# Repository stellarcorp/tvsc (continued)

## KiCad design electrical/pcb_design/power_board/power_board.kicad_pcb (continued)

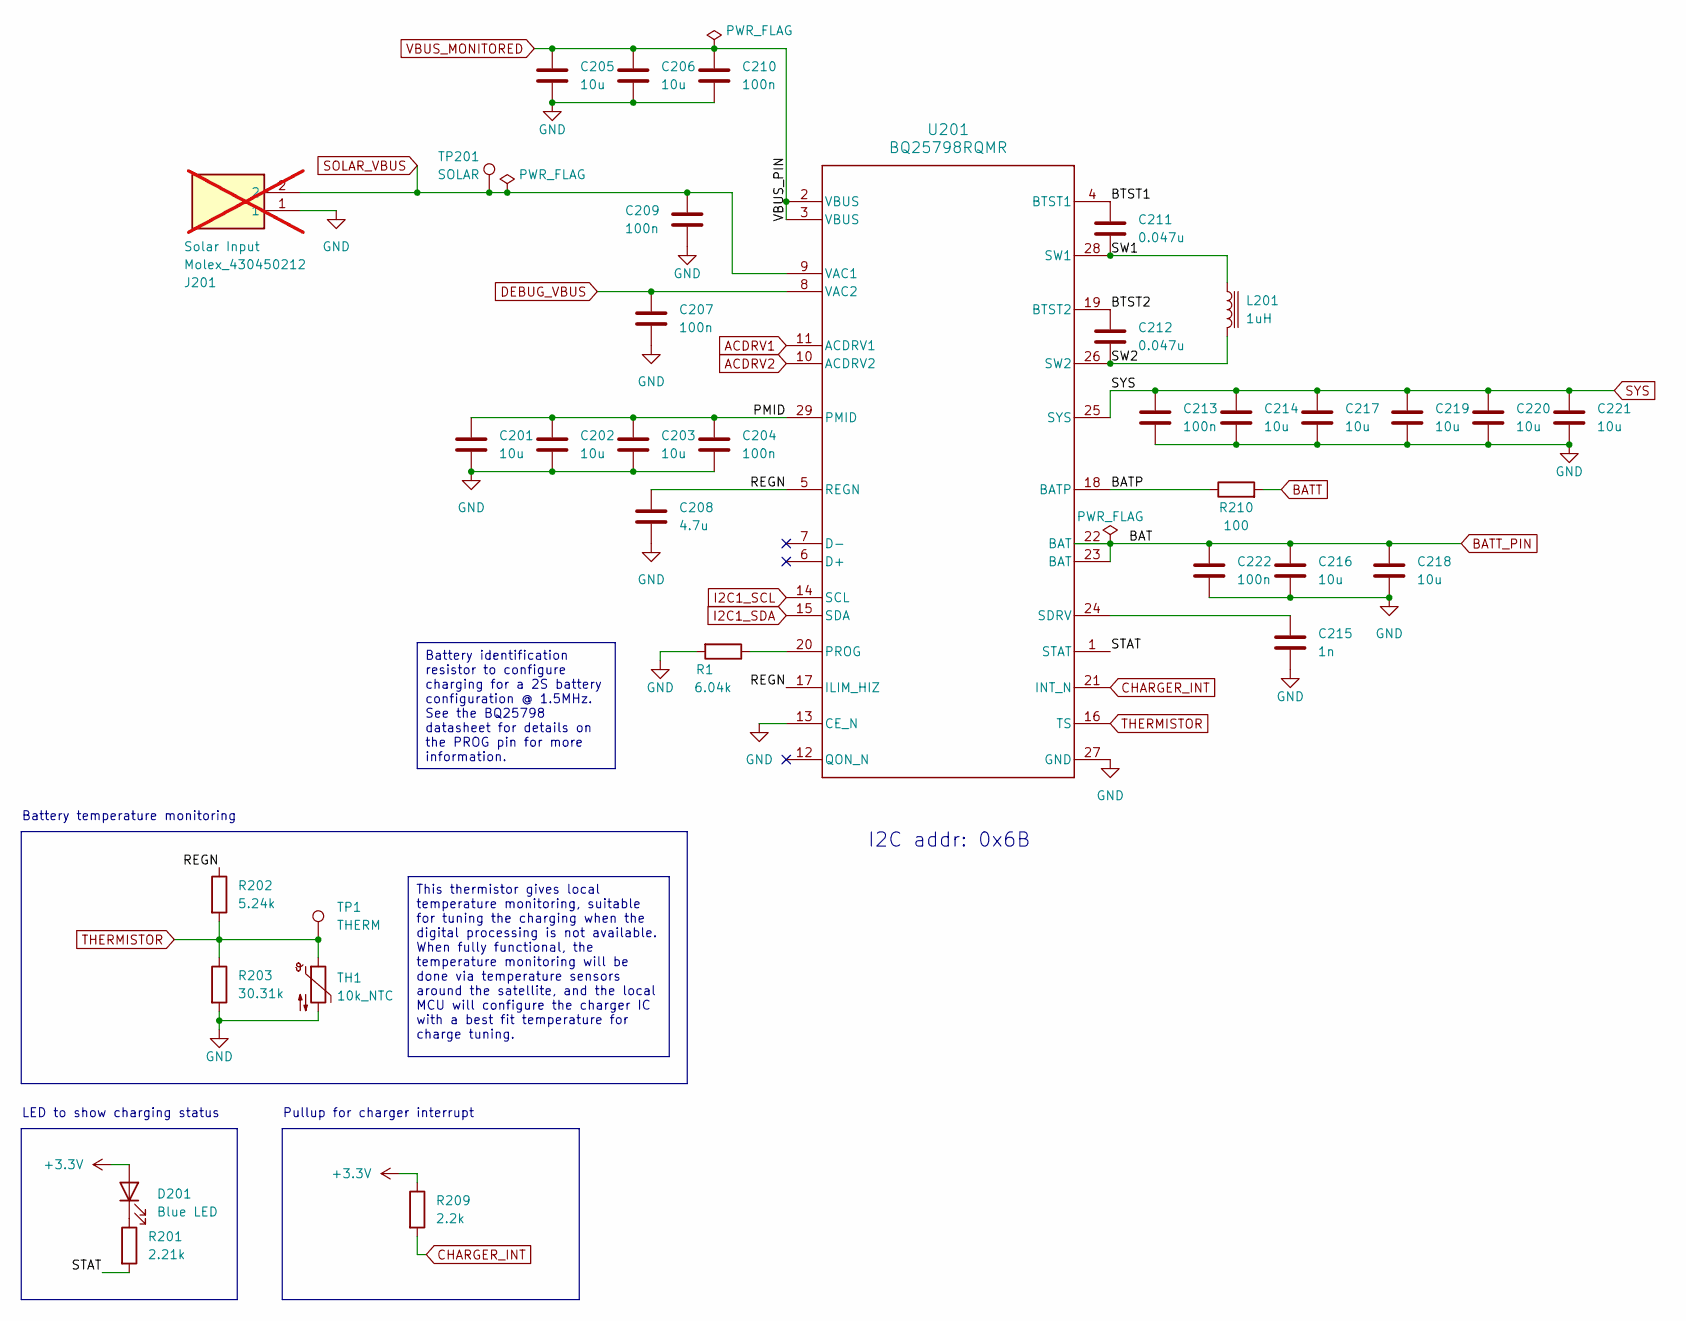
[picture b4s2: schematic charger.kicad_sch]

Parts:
C201, C202, C203, C205, C206, C214, C217, C219, C220, C221: 10u; Nondescript_C_0603_1608Metric; Manufacturer Part Number GRM188R61E106KA73D
C204, C207, C209, C210, C213, C222: 100n; Nondescript_C_0402_1005Metric; Manufacturer Part Number GCM155R71H104KE02J
C208: 4.7u; Nondescript_C_0603_1608Metric; MPN C86016
C211, C212: 0.047u; Nondescript_C_0402_1005Metric; Manufacturer Part Number CL05B473KA5NNNC
C215: 1n; Nondescript_C_0402_1005Metric; MPN C76947
C216, C218: 10u; Nondescript_C_0603_1608Metric; MPN C344022
D201: Blue LED; LED_0603_1608Metric; MPN C72041
J201: Molex_430450212; Manufacturer Part Number 430450212; not fitted
L201: 1uH; TDK_SPM6530; MPN C87572
R1: 6.04k; R_0603_1608Metric; MPN C114631
R201: 2.21k; Nondescript_R_0402_1005Metric; MPN C305298
R202: 5.24k; R_0402_1005Metric; MPN C170332
R203: 30.31k; R_0603_1608Metric; MPN C423049
R209: 2.2k; R_0402_1005Metric; MPN C517529
R210: 100; R_0603_1608Metric; MPN C105588
TH1: 10k_NTC; R_0402_1005Metric; MPN C209959
TP1: THERM; TestPoint_Pad_D2.5mm
TP201: SOLAR; TestPoint_Pad_D2.5mm
U201: BQ25798RQMR; RQM0029A-MFG; MPN C2876593

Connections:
+3.3V: D201.2 (A), R209.1; also elsewhere on the board
/Charger/BATP: R210.1, U201.18 (BATP)
/Charger/BTST1: C211.1, U201.4 (BTST1)
/Charger/BTST2: C212.1, U201.19 (BTST2)
/Charger/PMID: C201.1, C202.1, C203.1, C204.1, U201.29 (PMID)
/Charger/REGN: C208.1, R202.1, U201.5 (REGN), U201.17 (ILIM_HIZ)
/Charger/STAT: R201.2, U201.1 (STAT)
/Charger/SW1: C211.2, L201.1, U201.28 (SW1)
/Charger/SW2: C212.2, L201.2, U201.26 (SW2)
ACDRV1: U201.11 (ACDRV1); also elsewhere on the board
ACDRV2: U201.10 (ACDRV2); also elsewhere on the board
BATT: R210.2; also elsewhere on the board
BATT_PIN: C216.1, C218.1, C222.1, U201.22 (BAT), U201.23 (BAT); also elsewhere on the board
CHARGER_INT: R209.2, U201.21 (INT_N); also elsewhere on the board
DEBUG_VBUS: C207.1, U201.8 (VAC2); also elsewhere on the board
GND: C201.2, C202.2, C203.2, C204.2, C205.2, C206.2, C207.2, C208.2, C209.2, C210.2, C213.2, C214.2, C215.2, C216.2, C217.2, C218.2, C219.2, C220.2, C221.2, C222.2, J201.1, R1.2, R203.2, TH1.2, U201.13 (CE_N), U201.27 (GND); also elsewhere on the board
I2C1_SCL: U201.14 (SCL); also elsewhere on the board
I2C1_SDA: U201.15 (SDA); also elsewhere on the board
unnamed: D201.1 (K), R201.1
unnamed: R1.1, U201.20 (PROG)
unnamed: C215.1, U201.24 (SDRV)
SOLAR_VBUS: C209.1, J201.2, TP201.1, U201.9 (VAC1); also elsewhere on the board
SYS: C213.1, C214.1, C217.1, C219.1, C220.1, C221.1, U201.25 (SYS); also elsewhere on the board
THERMISTOR: R202.2, R203.1, TH1.1, TP1.1, U201.16 (TS); also elsewhere on the board
VBUS_MONITORED: C205.1, C206.1, C210.1, U201.2 (VBUS), U201.3 (VBUS); also elsewhere on the board

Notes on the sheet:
Battery identification resistor to configure charging for a 2S battery configuration @ 1.5MHz. See the BQ25798 datasheet for details on the PROG pin for more information.
This thermistor gives local temperature monitoring, suitable for tuning the charging when the digital processing is not available. When fully functional, the temperature monitoring will be done via temperature sensors around the satellite, and the local MCU will configure the charger IC with a best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
Pullup for charger interrupt
Battery temperature monitoring
I2C addr: 0x6B
LED to show charging status

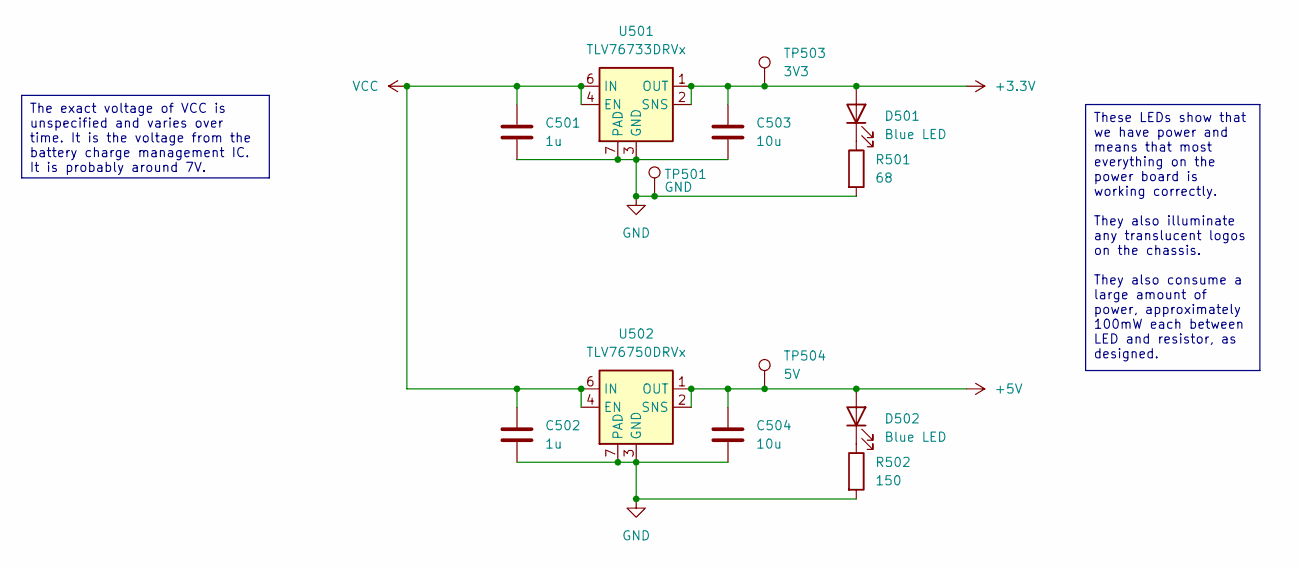
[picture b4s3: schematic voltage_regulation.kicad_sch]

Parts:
C501, C502: 1u; C_0805_2012Metric; MPN C726584
C503, C504: 10u; Nondescript_C_0603_1608Metric; MPN C344022
D501, D502: Blue LED; LED_0603_1608Metric; MPN C72041
R501: 68; R_0402_1005Metric; MPN C163455
R502: 150; R_0402_1005Metric; MPN C138054
TP501: GND; TestPoint_Pad_D2.5mm
TP503: 3V3; TestPoint_Pad_D2.5mm
TP504: 5V; TestPoint_Pad_D2.5mm
U501: TLV76733DRVx; WSON-6-1EP_2x2mm_P0.65mm_EP1x1.6mm_ThermalVias; MPN C2848334
U502: TLV76750DRVx; WSON-6-1EP_2x2mm_P0.65mm_EP1x1.6mm_ThermalVias; Manufacturer Part Number TLV76750DRVR

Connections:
+3.3V: C503.1, D501.2 (A), TP503.1, U501.1 (OUT), U501.2 (SNS); also elsewhere on the board
+5V: C504.1, D502.2 (A), TP504.1, U502.1 (OUT), U502.2 (SNS); also elsewhere on the board
GND: C501.2, C502.2, C503.2, C504.2, R501.2, R502.2, TP501.1, U501.3 (GND), U501.5 (GND), U501.7 (PAD), U502.3 (GND), U502.5 (GND), U502.7 (PAD); also elsewhere on the board
unnamed: D501.1 (K), R501.1
unnamed: D502.1 (K), R502.1
VCC: C501.1, C502.1, U501.4 (EN), U501.6 (IN), U502.4 (EN), U502.6 (IN); also elsewhere on the board

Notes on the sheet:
These LEDs show that we have power and means that most everything on the power board is working correctly. They also illuminate any translucent logos on the chassis. They also consume a large amount of power, approximately 100mW each between LED and resistor, as designed.
The exact voltage of VCC is unspecified and varies over time. It is the voltage from the battery charge management IC. It is probably around 7V.

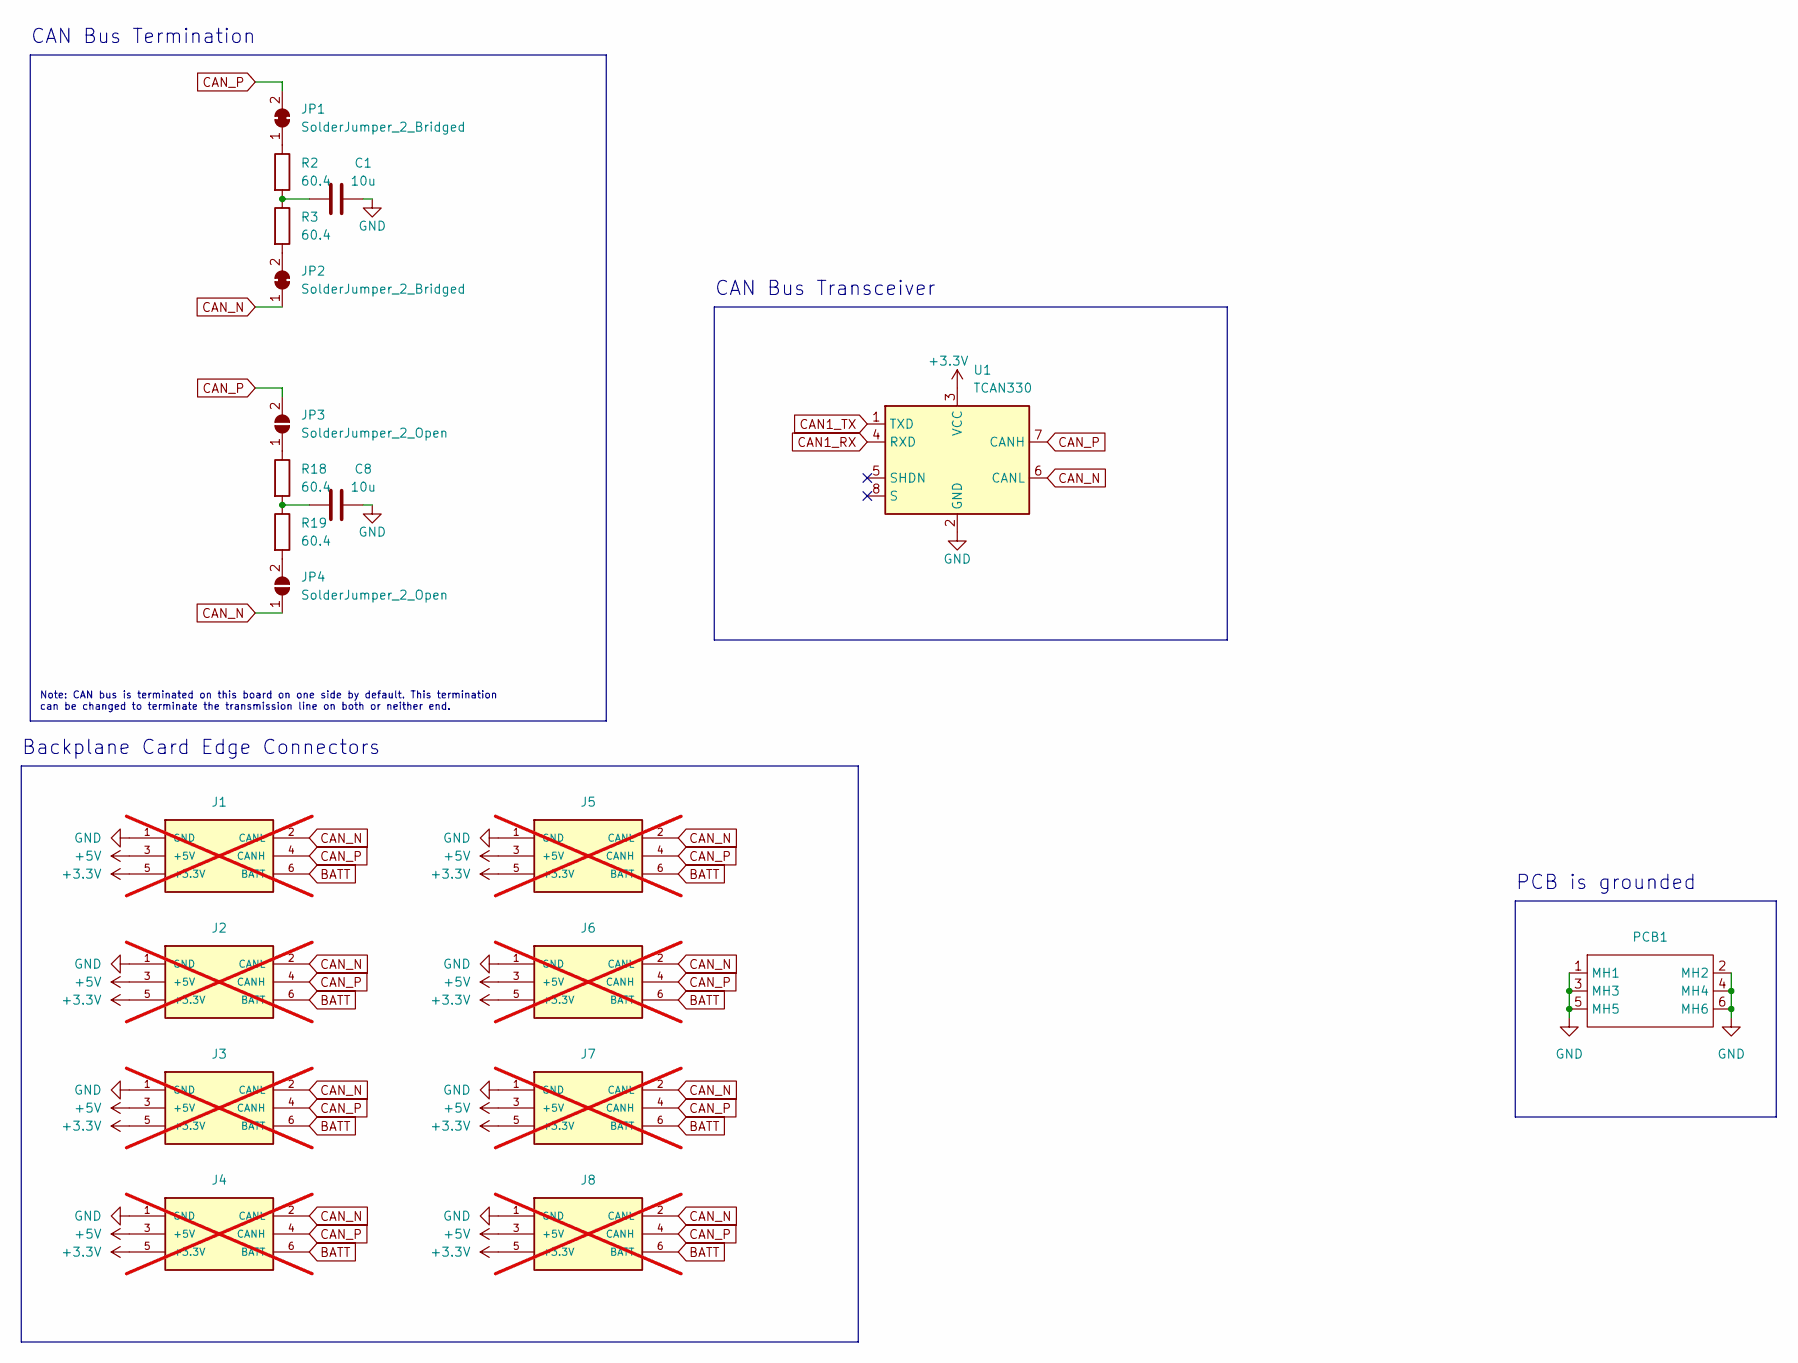
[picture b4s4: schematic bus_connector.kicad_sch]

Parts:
C1, C8: 10u; Nondescript_C_0603_1608Metric; MPN C344022
J1, J2, J3, J4, J5, J6, J7, J8: TE_Connectivity_7-5530843-7; Manufacturer Part Number 7-5530843-7; not fitted
JP1, JP2: SolderJumper_2_Bridged; SolderJumper-2_P1.3mm_Bridged_RoundedPad1.0x1.5mm
JP3, JP4: SolderJumper_2_Open; SolderJumper-2_P1.3mm_Open_RoundedPad1.0x1.5mm
PCB1: Interior_Side_Panel_PCB_Shape
R2, R3, R18, R19: 60.4; R_0402_1005Metric; MPN C60310
U1: TCAN330; SOT-23-8; Manufacturer Part Number TCAN330DCNR

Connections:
+3.3V: J1.5 (+3.3V), J2.5 (+3.3V), J3.5 (+3.3V), J4.5 (+3.3V), J5.5 (+3.3V), J6.5 (+3.3V), J7.5 (+3.3V), J8.5 (+3.3V), U1.3 (VCC); also elsewhere on the board
+5V: J1.3 (+5V), J2.3 (+5V), J3.3 (+5V), J4.3 (+5V), J5.3 (+5V), J6.3 (+5V), J7.3 (+5V), J8.3 (+5V); also elsewhere on the board
BATT: J1.6 (BATT), J2.6 (BATT), J3.6 (BATT), J4.6 (BATT), J5.6 (BATT), J6.6 (BATT), J7.6 (BATT), J8.6 (BATT); also elsewhere on the board
CAN1_RX: U1.4 (RXD); also elsewhere on the board
CAN1_TX: U1.1 (TXD); also elsewhere on the board
CAN_N: J1.2 (CANL), J2.2 (CANL), J3.2 (CANL), J4.2 (CANL), J5.2 (CANL), J6.2 (CANL), J7.2 (CANL), J8.2 (CANL), JP2.1 (A), JP4.1 (A), U1.6 (CANL)
CAN_P: J1.4 (CANH), J2.4 (CANH), J3.4 (CANH), J4.4 (CANH), J5.4 (CANH), J6.4 (CANH), J7.4 (CANH), J8.4 (CANH), JP1.2 (B), JP3.2 (B), U1.7 (CANH)
GND: C1.2, C8.2, J1.1 (GND), J2.1 (GND), J3.1 (GND), J4.1 (GND), J5.1 (GND), J6.1 (GND), J7.1 (GND), J8.1 (GND), PCB1.1 (MH1), PCB1.2 (MH2), PCB1.3 (MH3), PCB1.4 (MH4), PCB1.5 (MH5), PCB1.6 (MH6), U1.2 (GND); also elsewhere on the board
unnamed: C1.1, R2.2, R3.1
unnamed: C8.1, R18.2, R19.1
unnamed: JP1.1 (A), R2.1
unnamed: JP2.2 (B), R3.2
unnamed: JP3.1 (A), R18.1
unnamed: JP4.2 (B), R19.2

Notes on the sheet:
Note: CAN bus is terminated on this board on one side by default. This termination can be changed to terminate the transmission line on both or neither end.
PCB is grounded
CAN Bus Transceiver
CAN Bus Termination
Backplane Card Edge Connectors

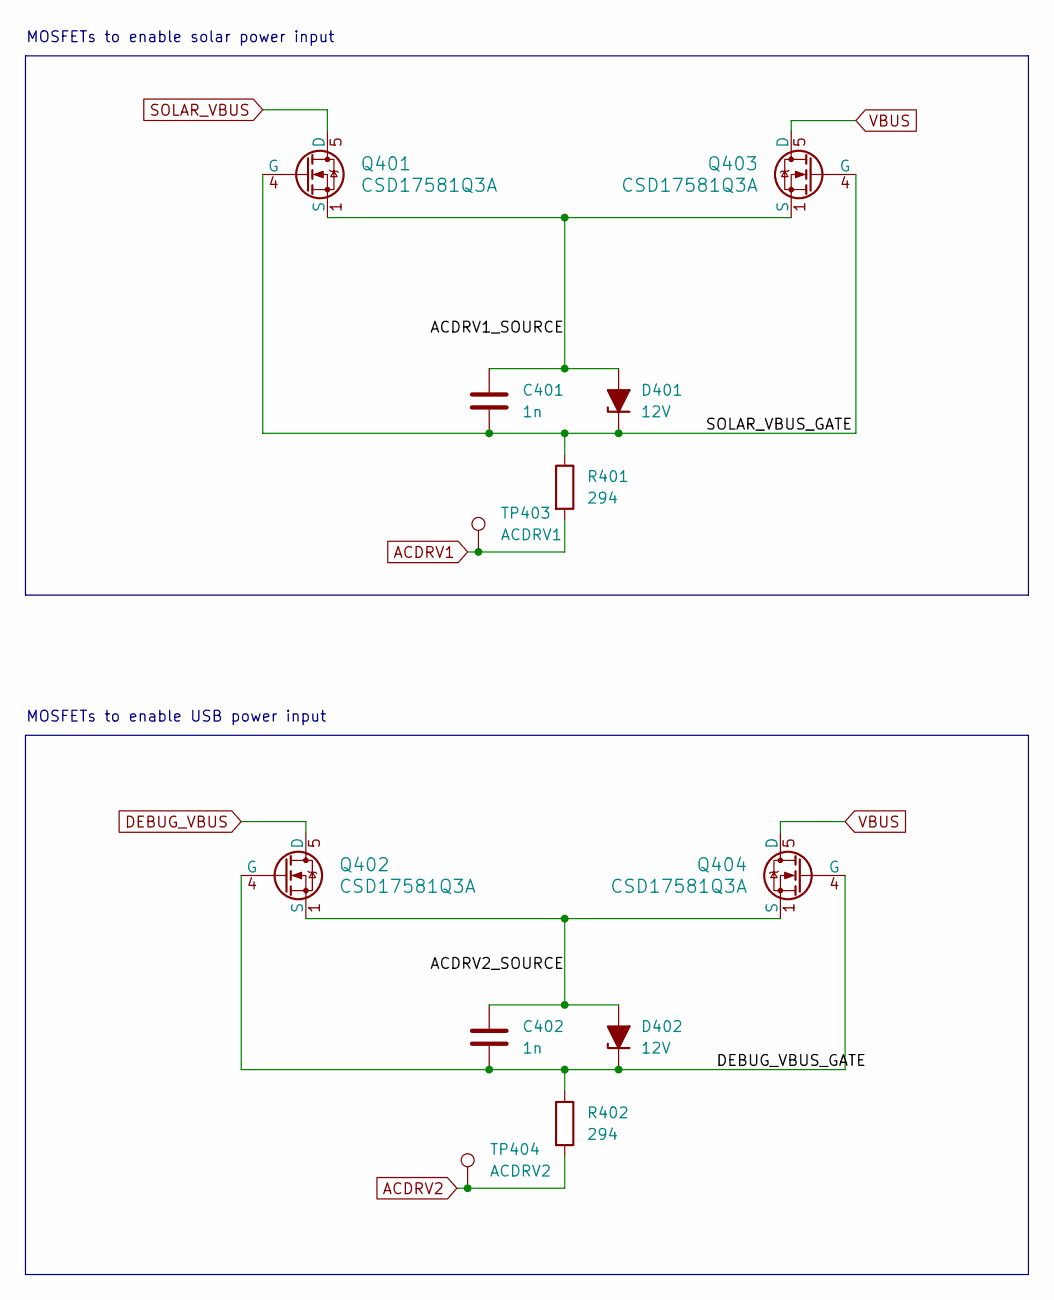
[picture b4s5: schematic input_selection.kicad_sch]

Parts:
C401, C402: 1n; Nondescript_C_0402_1005Metric; Manufacturer Part Number GRM1555C1H102JA01D
D401, D402: 12V; D_SOD-523; Manufacturer Part Number BZT52C12T-7
Q401, Q402, Q403, Q404: CSD17581Q3A; Q3A_TEX; MPN C2861705
R401, R402: 294; R_0603_1608Metric; Manufacturer Part Number RC0603FR-07294RL
TP403: ACDRV1; TestPoint_Pad_D2.5mm
TP404: ACDRV2; TestPoint_Pad_D2.5mm

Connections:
/Input Selection/ACDRV1_SOURCE: C401.1, D401.2 (A), Q401.1 (S), Q403.1 (S)
/Input Selection/ACDRV2_SOURCE: C402.1, D402.2 (A), Q402.1 (S), Q404.1 (S)
/Input Selection/DEBUG_VBUS_GATE: C402.2, D402.1 (K), Q402.4 (G), Q404.4 (G), R402.1
/Input Selection/SOLAR_VBUS_GATE: C401.2, D401.1 (K), Q401.4 (G), Q403.4 (G), R401.1
ACDRV1: R401.2, TP403.1; also elsewhere on the board
ACDRV2: R402.2, TP404.1; also elsewhere on the board
DEBUG_VBUS: Q402.5 (D); also elsewhere on the board
SOLAR_VBUS: Q401.5 (D); also elsewhere on the board
VBUS: Q403.5 (D), Q404.5 (D); also elsewhere on the board

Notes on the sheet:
MOSFETs to enable USB power input
MOSFETs to enable solar power input

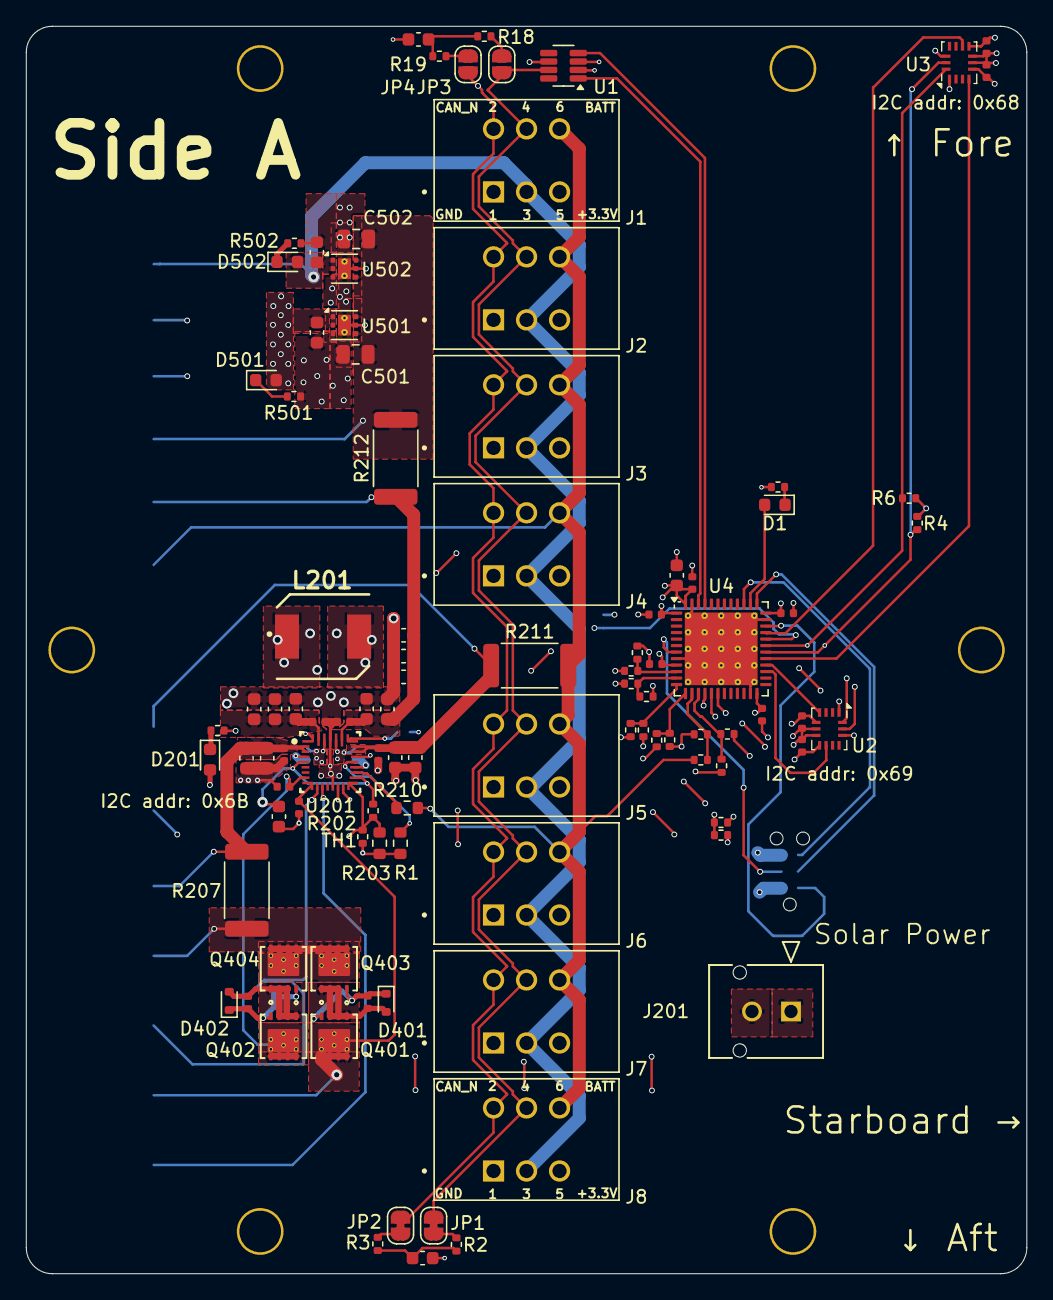
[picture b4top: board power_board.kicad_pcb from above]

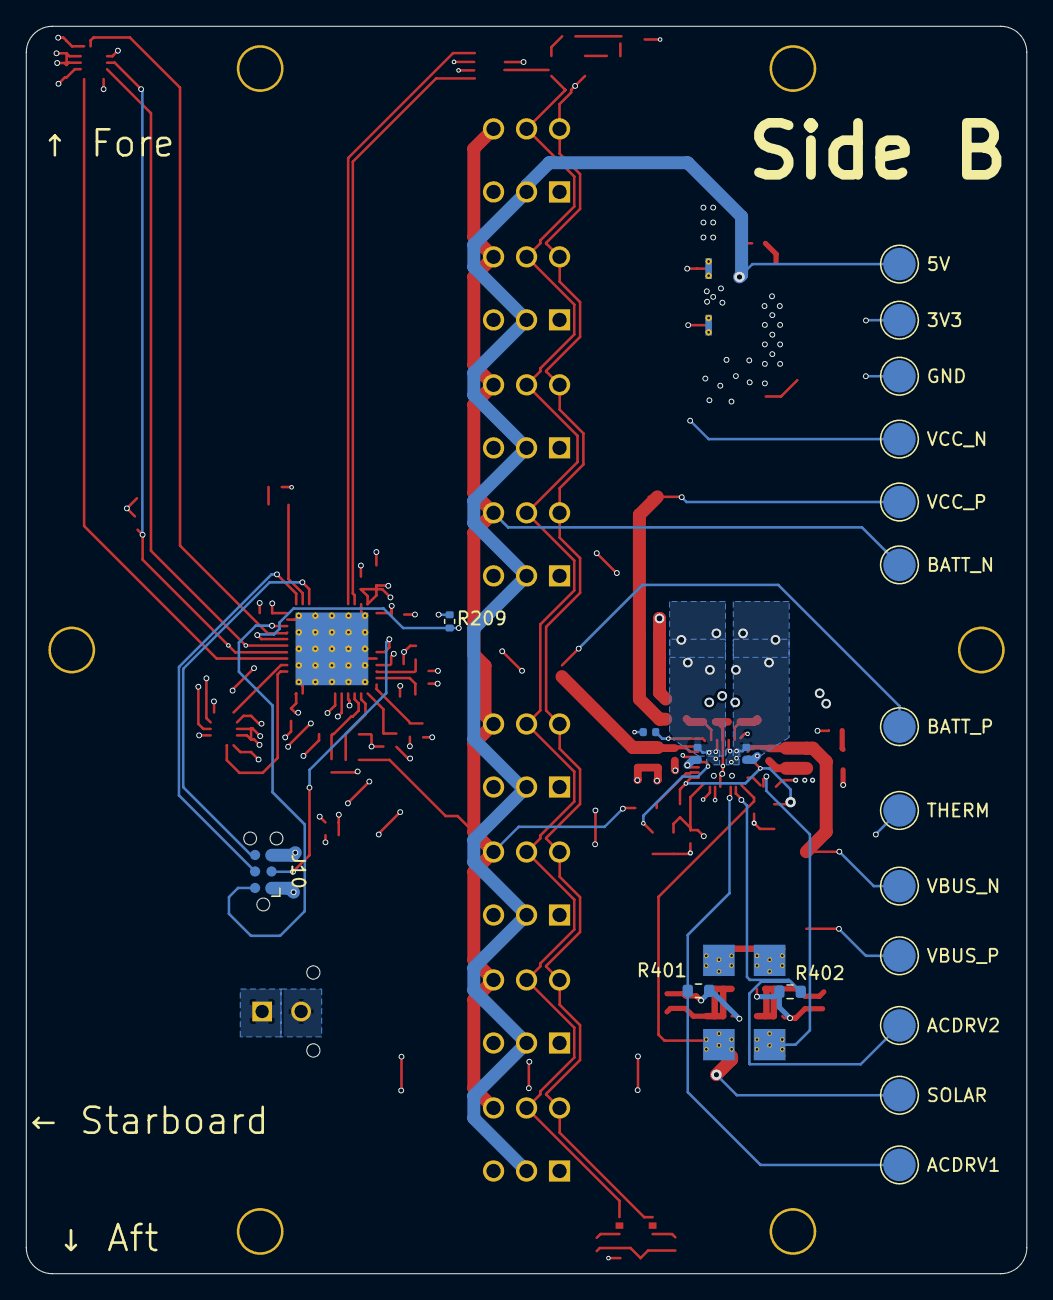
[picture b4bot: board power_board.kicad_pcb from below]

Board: 4 copper layers, 77.0 x 96.0 mm, 121 parts (20 on the bottom side), 62 nets.

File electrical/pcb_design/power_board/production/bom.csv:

Designator,Footprint,Quantity,Value,LCSC Part #
"C1, C2, C201, C202, C203, C205, C206, C214, C216, C217, C218, C219, C220, C221, C503, C504, C8",Nondescript_C_0603_1608Metric,17,10u,C344022
"C10, C11, C12, C204, C207, C209, C210, C213, C222, C4, C5, C6, C7, C9",Nondescript_C_0402_1005Metric,14,100n,C2649549
C208,Nondescript_C_0603_1608Metric,1,4.7u,C86016
"C211, C212",Nondescript_C_0402_1005Metric,2,0.047u,C318631
"C215, C401, C402",Nondescript_C_0402_1005Metric,3,1n,C76947
C3,Nondescript_C_0402_1005Metric,1,10n,C5189696
"C501, C502",0805,2,1u,C726584
"D1, D201, D501, D502",0603,4,Blue LED,C72041
"D401, D402",D_SOD-523,2,12V,C507911
"JP1, JP2",SolderJumper-2_P1.3mm_Bridged_RoundedPad1.0x1.5mm,2,SolderJumper_2_Bridged,
"JP3, JP4",SolderJumper-2_P1.3mm_Open_RoundedPad1.0x1.5mm,2,SolderJumper_2_Open,
L201,TDK_SPM6530,1,1uH,C87572
"Q401, Q402, Q403, Q404",Q3A_TEX,4,CSD17581Q3A,C2861705
R1,0603,1,6.04k,C114631
"R10, R12, R14, R16, R21, R22, R5, R8",Nondescript_R_0402_1005Metric,8,475k,C25791
"R11, R13, R15, R17, R7, R9",Nondescript_R_0402_1005Metric,6,187k,C25761
"R18, R19, R2, R3",0402,4,60.4,C60310
"R20, R201",Nondescript_R_0402_1005Metric,2,2.21k,C305298
R202,0402,1,5.24k,C170332
R203,0603,1,30.31k,C423049
"R207, R211, R212",2512,3,0.01,C844296
R209,0402,1,2.2k,C517529
R210,0603,1,100,C105588
"R4, R6",0402,2,1k5,C25867
"R401, R402",0603,2,294,C185345
R501,0402,1,68,C163455
R502,0402,1,150,C138054
TH1,0402,1,10k_NTC,C209959
TP1,TestPoint_Pad_D2.5mm,1,THERM,
TP201,TestPoint_Pad_D2.5mm,1,SOLAR,
TP203,TestPoint_Pad_D2.5mm,1,VBUS_P,
TP206,TestPoint_Pad_D2.5mm,1,VBUS_N,
TP210,TestPoint_Pad_D2.5mm,1,BATT_P,
TP211,TestPoint_Pad_D2.5mm,1,BATT_N,
TP213,TestPoint_Pad_D2.5mm,1,VCC_P,
TP214,TestPoint_Pad_D2.5mm,1,VCC_N,
TP403,TestPoint_Pad_D2.5mm,1,ACDRV1,
TP404,TestPoint_Pad_D2.5mm,1,ACDRV2,
TP501,TestPoint_Pad_D2.5mm,1,GND,
TP503,TestPoint_Pad_D2.5mm,1,3V3,
TP504,TestPoint_Pad_D2.5mm,1,5V,
U1,SOT-23-8,1,TCAN330,C2877587
"U2, U3",Bosch_LGA-14_3x2.5mm_P0.5mm,2,BMI323,C5368700
U201,RQM0029A-MFG,1,BQ25798RQMR,C2876593
U4,QFN-48-1EP_7x7mm_P0.5mm_EP5.6x5.6mm_ThermalVias,1,STM32L452CEU6,C222355
U501,WSON-6-1EP_2x2mm_P0.65mm_EP1x1.6mm_ThermalVias,1,TLV76733DRVx,C2848334
U502,WSON-6-1EP_2x2mm_P0.65mm_EP1x1.6mm_ThermalVias,1,TLV76750DRVx,C2872569

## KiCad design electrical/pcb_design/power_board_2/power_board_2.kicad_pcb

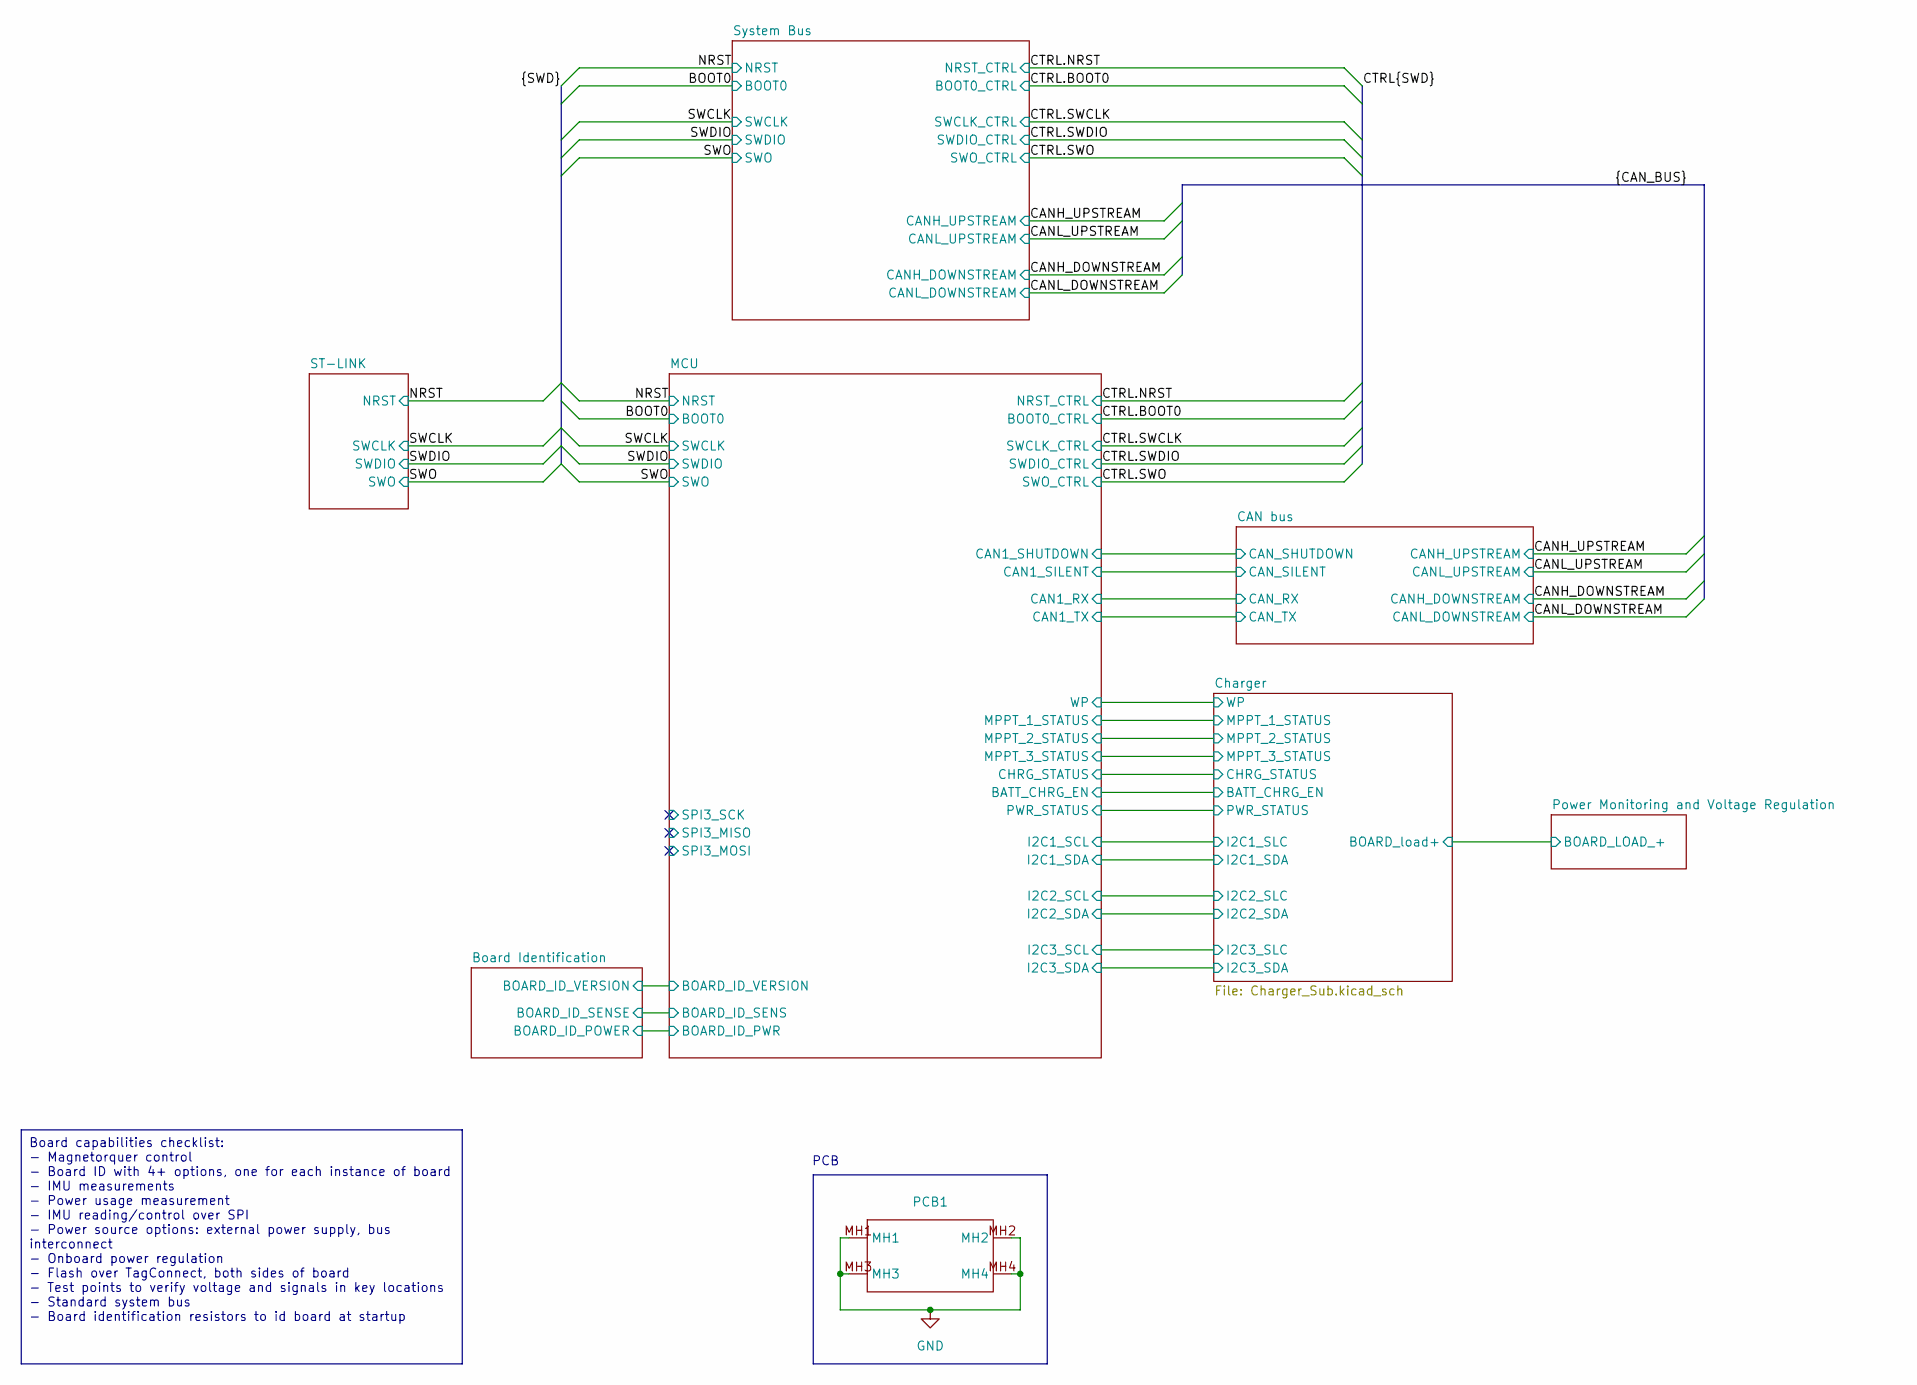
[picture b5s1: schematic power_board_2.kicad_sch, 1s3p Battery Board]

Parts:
PCB1: Core_Board_Shape_Space_Invader_2

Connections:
GND: PCB1.MH1, PCB1.MH2, PCB1.MH3, PCB1.MH4; also elsewhere on the board

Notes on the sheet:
Board capabilities checklist: - Magnetorquer control - Board ID with 4+ options, one for each instance of board - IMU measurements - Power usage measurement - IMU reading/control over SPI - Power source options: external power supply, bus interconnect - Onboard power regulation - Flash over TagConn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
PCB

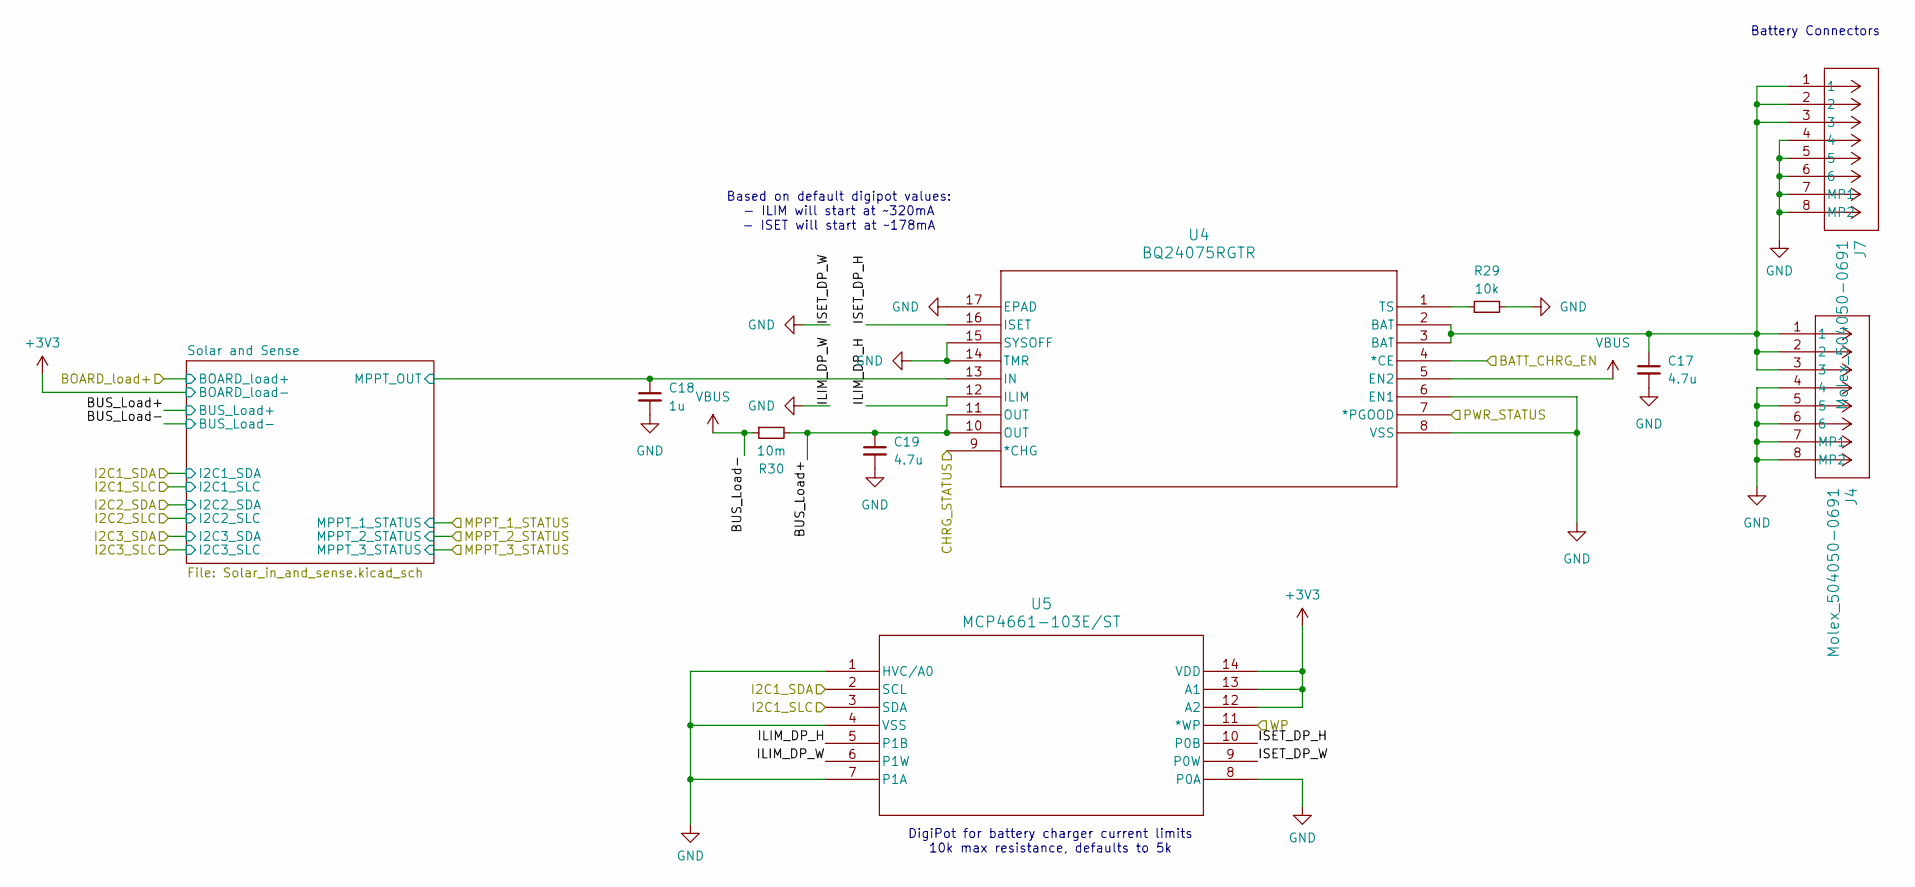
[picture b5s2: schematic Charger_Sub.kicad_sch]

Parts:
C17, C19: 4.7u; Nondescript_C_0402_1005Metric
C18: 1u; Nondescript_C_0402_1005Metric
J4, J7: Molex_504050-0691; Manufacturer Part Number 504050-0691
R29: 10k; Nondescript_R_0402_1005Metric
R30: 10m; R_2512_6332Metric
U4: BQ24075RGTR; BQ2407x
U5: MCP4661-103E/ST; MCP4661

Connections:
+3V3: U5.12 (A2), U5.13 (A1), U5.14 (VDD); also elsewhere on the board
/Charger/BATT_CHRG_EN: U4.4 (*CE); also elsewhere on the board
/Charger/BUS_Load+: C19.1, R30.2, U4.10 (OUT), U4.11 (OUT); also elsewhere on the board
/Charger/CHRG_STATUS: U4.9 (*CHG); also elsewhere on the board
/Charger/I2C1_SDA: U5.2 (SCL); also elsewhere on the board
/Charger/I2C1_SLC: U5.3 (SDA); also elsewhere on the board
/Charger/ILIM_DP_H: U4.12 (ILIM), U5.5 (P1B)
/Charger/ISET_DP_H: U4.16 (ISET), U5.10 (P0B)
/Charger/PWR_STATUS: U4.7 (*PGOOD); also elsewhere on the board
/Charger/Solar and Sense/MPPT_OUT: C18.1, U4.13 (IN); also elsewhere on the board
/Charger/WP: U5.11 (*WP); also elsewhere on the board
GND: C17.2, C18.2, C19.2, J4.4, J4.5, J4.6, J4.7 (MP1), J4.8 (MP2), J7.4, J7.5, J7.6, J7.7 (MP1), J7.8 (MP2), R29.2, U4.6 (EN1), U4.8 (VSS), U4.14 (TMR), U4.15 (SYSOFF), U4.17 (EPAD), U5.1 (HVC/A0), U5.4 (VSS), U5.6 (P1W), U5.7 (P1A), U5.8 (P0A), U5.9 (P0W); also elsewhere on the board
unnamed: C17.1, J4.1, J4.2, J4.3, J7.1, J7.2, J7.3, U4.2 (BAT), U4.3 (BAT)
unnamed: R29.1, U4.1 (TS)
VBUS: R30.1, U4.5 (EN2); also elsewhere on the board

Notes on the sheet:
Based on default digipot values: - ILIM will start at ~320mA - ISET will start at ~178mA
Battery Connectors
DigiPot for battery charger current limits 10k max resistance, defaults to 5k

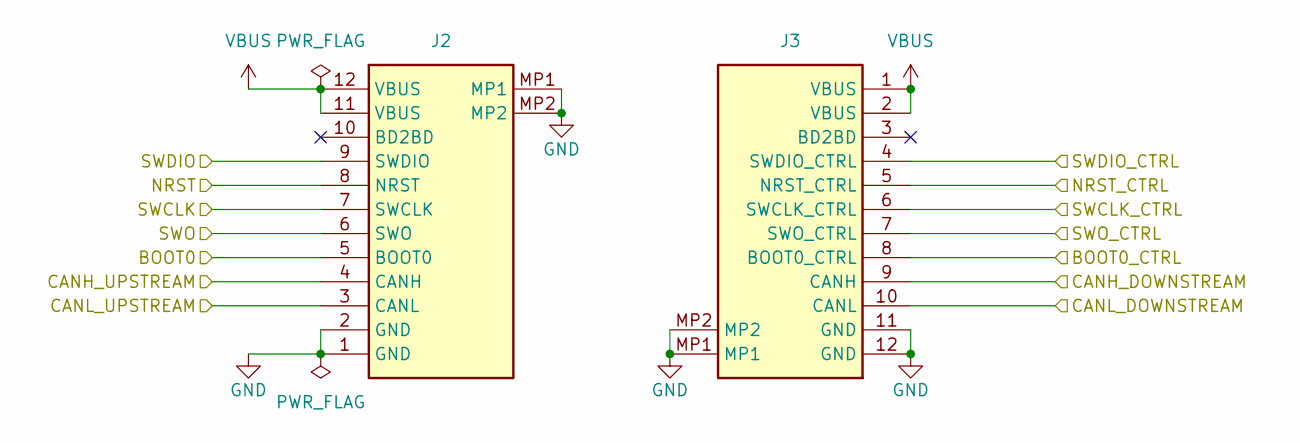
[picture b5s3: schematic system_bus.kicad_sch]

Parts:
J2: Molex_504050-1291; Bus Connector (Target); Manufacturer Part Number 504050-1291
J3: Molex_504050-1291; Bus Connector (Control); Manufacturer Part Number 504050-1291

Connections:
/BOOT0: J2.5 (BOOT0); also elsewhere on the board
/CANH_DOWNSTREAM: J3.9 (CANH); also elsewhere on the board
/CANH_UPSTREAM: J2.4 (CANH); also elsewhere on the board
/CANL_DOWNSTREAM: J3.10 (CANL); also elsewhere on the board
/CANL_UPSTREAM: J2.3 (CANL); also elsewhere on the board
/CTRL.BOOT0: J3.8 (BOOT0_CTRL); also elsewhere on the board
/CTRL.NRST: J3.5 (NRST_CTRL); also elsewhere on the board
/CTRL.SWCLK: J3.6 (SWCLK_CTRL); also elsewhere on the board
/CTRL.SWDIO: J3.4 (SWDIO_CTRL); also elsewhere on the board
/CTRL.SWO: J3.7 (SWO_CTRL); also elsewhere on the board
/NRST: J2.8 (NRST); also elsewhere on the board
/SWCLK: J2.7 (SWCLK); also elsewhere on the board
/SWDIO: J2.9 (SWDIO); also elsewhere on the board
/SWO: J2.6 (SWO); also elsewhere on the board
GND: J2.1 (GND), J2.2 (GND), J2.MP1, J2.MP2, J3.11 (GND), J3.12 (GND), J3.MP1, J3.MP2; also elsewhere on the board
VBUS: J2.11 (VBUS), J2.12 (VBUS), J3.1 (VBUS), J3.2 (VBUS); also elsewhere on the board
